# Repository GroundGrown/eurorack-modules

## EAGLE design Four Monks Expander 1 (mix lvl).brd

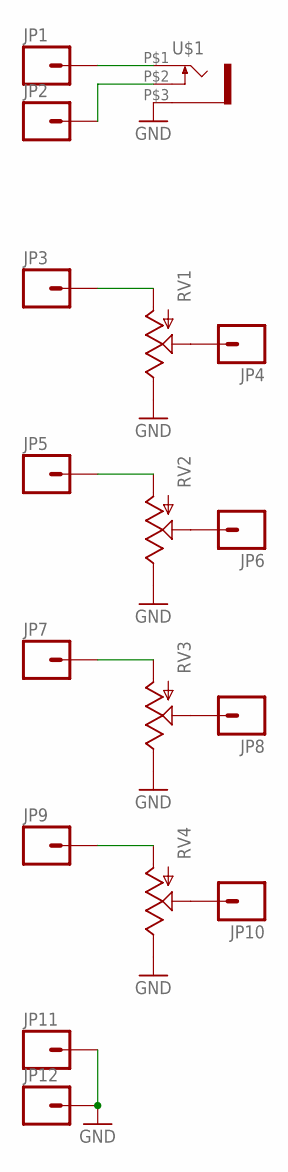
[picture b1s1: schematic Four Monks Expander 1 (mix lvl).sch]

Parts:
JP1, JP2, JP3, JP4, JP5, JP6, JP7, JP8, JP9, JP10, JP11, JP12: M01PTH; 1X01
RV1, RV2, RV3, RV4: POT; ALPS_POT
U$1: WQP-PJ301M-12_JACK

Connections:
GND: JP11.1, JP12.1, RV1.P$1 (E), RV2.P$1 (E), RV3.P$1 (E), RV4.P$1 (E), U$1.P$3 (1)
unnamed: JP4.1, RV1.P$2 (S)
unnamed: JP6.1, RV2.P$2 (S)
unnamed: JP8.1, RV3.P$2 (S)
unnamed: JP10.1, RV4.P$2 (S)
unnamed: JP9.1, RV4.P$3 (A)
unnamed: JP7.1, RV3.P$3 (A)
unnamed: JP5.1, RV2.P$3 (A)
unnamed: JP3.1, RV1.P$3 (A)
unnamed: JP1.1, U$1.P$1 (2)
unnamed: JP2.1, U$1.P$2 (3)

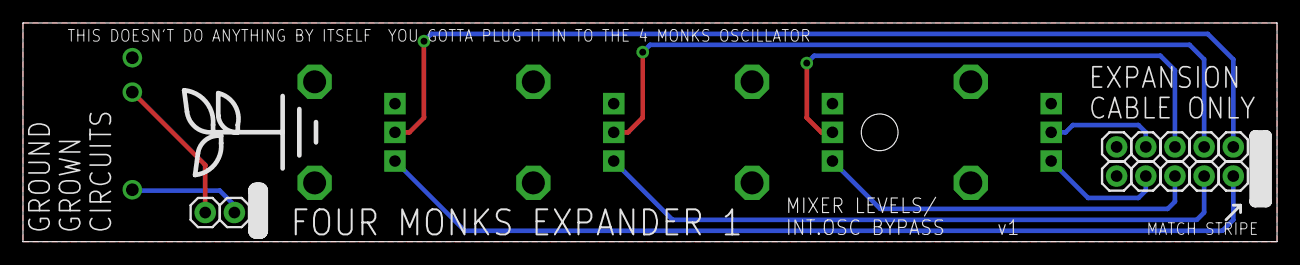
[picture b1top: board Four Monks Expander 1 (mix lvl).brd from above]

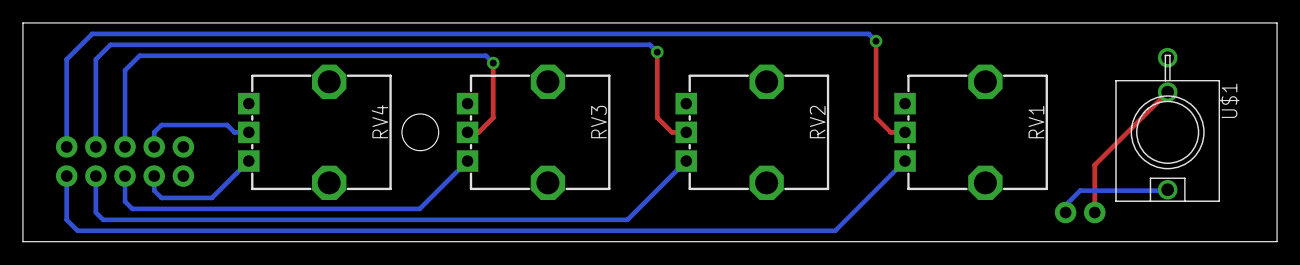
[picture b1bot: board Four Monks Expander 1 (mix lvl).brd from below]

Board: 2 copper layers, 109.2 x 19.1 mm, 18 parts (5 on the bottom side), 11 nets.

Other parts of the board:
U$2: LOGO_MED

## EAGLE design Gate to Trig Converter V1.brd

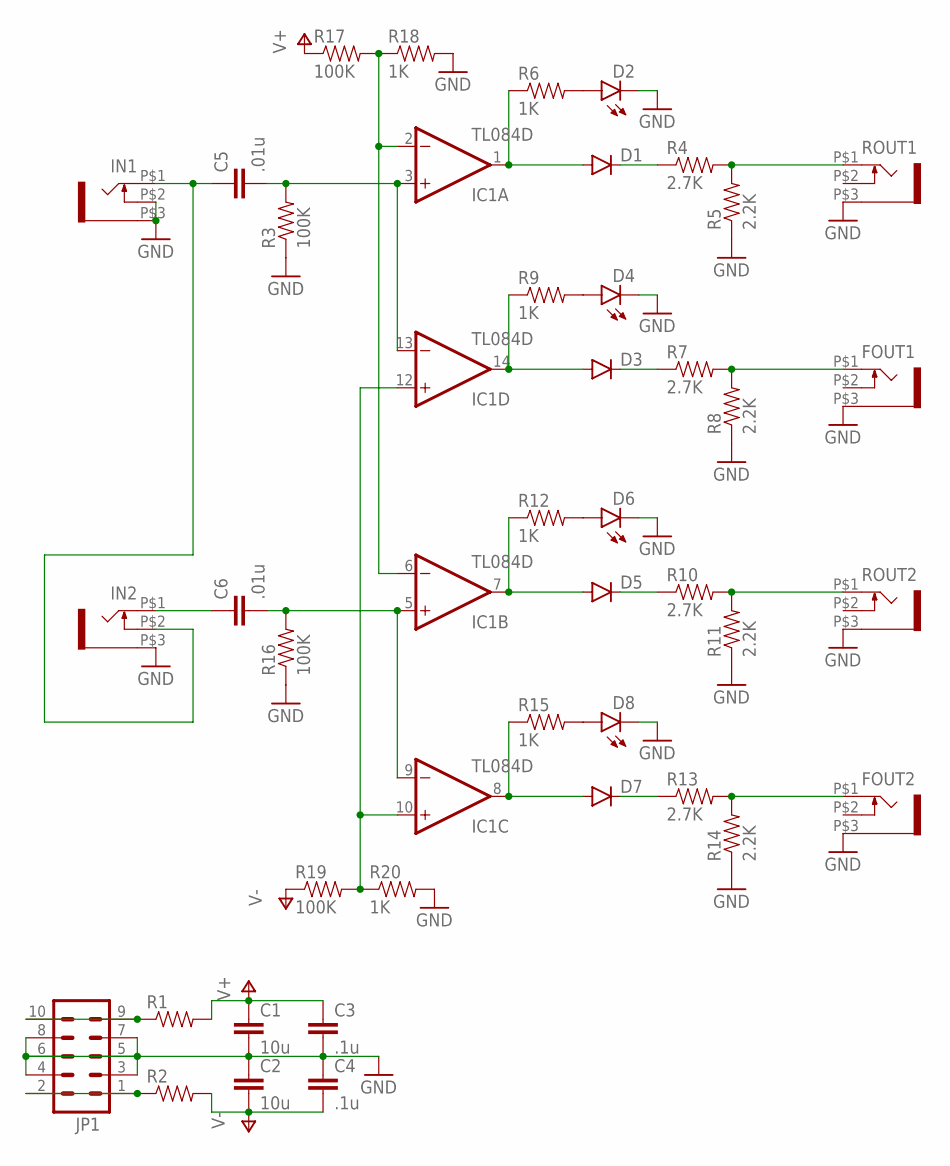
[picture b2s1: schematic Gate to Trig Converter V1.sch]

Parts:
C1, C2: 10u; 1206
C3, C4: .1u; 0805
C5, C6: .01u; 0805
D1, D3, D5, D7: DIODESOD123; SOD-123
D2, D4, D6, D8: LED3MM
FOUT1, FOUT2: WQP-PJ301M-12_JACK
IC1: TL084D; SO14
IN1, IN2: WQP-PJ301M-12_JACK
JP1: M05X2PTH; AVR_ICSP
R1, R2: RESISTOR0805-RES; 0805
R3, R16, R17, R19: 100K; 0805
R4, R7, R10, R13: 2.7K; 0805
R5, R8, R11, R14: 2.2K; 0805
R6, R9, R12, R15, R18, R20: 1K; 0805
ROUT1, ROUT2: WQP-PJ301M-12_JACK

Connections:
GND: C1.2, C2.1, C3.2, C4.1, D2.K (C), D4.K (C), D6.K (C), D8.K (C), FOUT1.P$3 (1), FOUT2.P$3 (1), IN1.P$2 (3), IN1.P$3 (1), IN2.P$3 (1), JP1.3, JP1.4, JP1.5, JP1.6, JP1.7, JP1.8, R3.1, R5.1, R8.1, R11.1, R14.1, R16.1, R18.2, R20.2, ROUT1.P$3 (1), ROUT2.P$3 (1)
unnamed: JP1.9, JP1.10, R1.1
unnamed: JP1.1, JP1.2, R2.1
unnamed: R4.2, R5.2, ROUT1.P$1 (2)
unnamed: D2.A, R6.2
unnamed: C5.1, IN1.P$1 (2), IN2.P$2 (3)
unnamed: C5.2, IC1.3 (+IN), IC1.13 (-IN), R3.2
unnamed: D1.A, IC1.1 (OUT), R6.1
unnamed: D1.C, R4.1
unnamed: FOUT1.P$1 (2), R7.2, R8.2
unnamed: D4.A, R9.2
unnamed: D3.A, IC1.14 (OUT), R9.1
unnamed: D3.C, R7.1
unnamed: R10.2, R11.2, ROUT2.P$1 (2)
unnamed: D6.A, R12.2
unnamed: D5.A, IC1.7 (OUT), R12.1
unnamed: D5.C, R10.1
unnamed: FOUT2.P$1 (2), R13.2, R14.2
unnamed: D8.A, R15.2
unnamed: D7.A, IC1.8 (OUT), R15.1
unnamed: D7.C, R13.1
unnamed: C6.1, IN2.P$1 (2)
unnamed: C6.2, IC1.5 (+IN), IC1.9 (-IN), R16.2
unnamed: IC1.2 (-IN), IC1.6 (-IN), R17.2, R18.1
unnamed: IC1.10 (+IN), IC1.12 (+IN), R19.2, R20.1
V+: C1.1, C3.1, IC1.4 (V+), R1.2, R17.1
V-: C2.2, C4.2, IC1.11 (V-), R2.2, R19.1

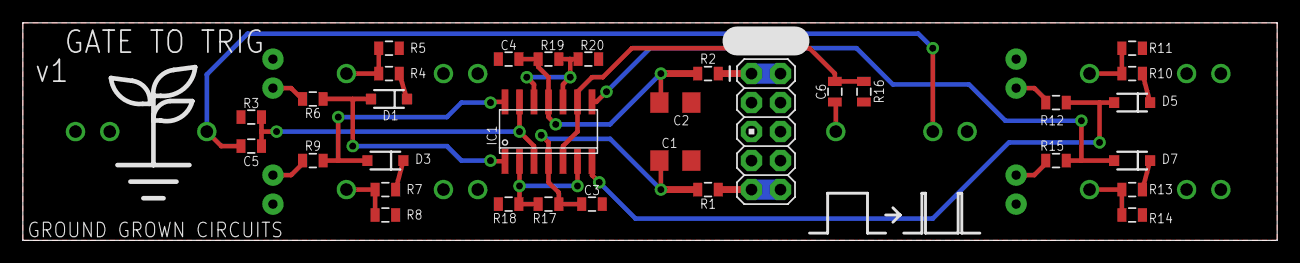
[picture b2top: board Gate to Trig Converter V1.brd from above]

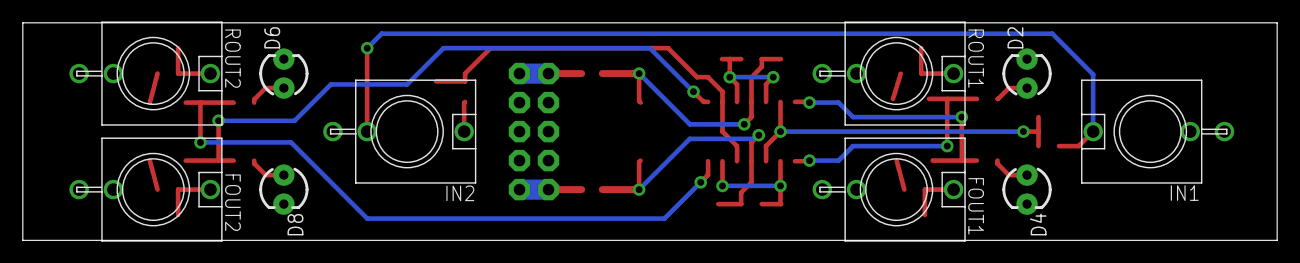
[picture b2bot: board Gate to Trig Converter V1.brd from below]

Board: 2 copper layers, 109.9 x 19.1 mm, 43 parts (10 on the bottom side), 27 nets.

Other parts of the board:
U$1: LOGO_MED

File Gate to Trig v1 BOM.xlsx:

| MAIN BOARD
2 | FERRITE BEAD | R1, R2
6 | 1K | R6, R9, R12, R15, R18, R20
4 | 2.2K | R5, R8, R11, R14
4 | 2.7K | R4, R7, R10, R13
4 | 100K | R3, R16, R17, R19
2 | .01u | C5, C6
2 | .1u | C3, C4
2 | 10u | C1, C2 | 1206
4 | 4148 | D1, D3, D5, D7
4 | 3mm LED | D2, D4, D6, D8
1 | TL084 | IC1
1 | 2x5 .1" Header Male
6 | WQP-PJ301M-12_JACK | IN1, IN2, ROUT1, ROUT2, FOUT1 FOUT2

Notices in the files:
parts and their libraries:
SparkFun-Connectors: Licensing: Creative Commons ShareAlike 4.0 International - https://creativecommons.org/licenses/by-sa/4.0
